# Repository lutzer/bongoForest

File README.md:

# BONGO FOREST

### Important

* Dont run arduino pros on more than 5 V on the RAW Pin. use seperate voltage regulator or **they will burn**.

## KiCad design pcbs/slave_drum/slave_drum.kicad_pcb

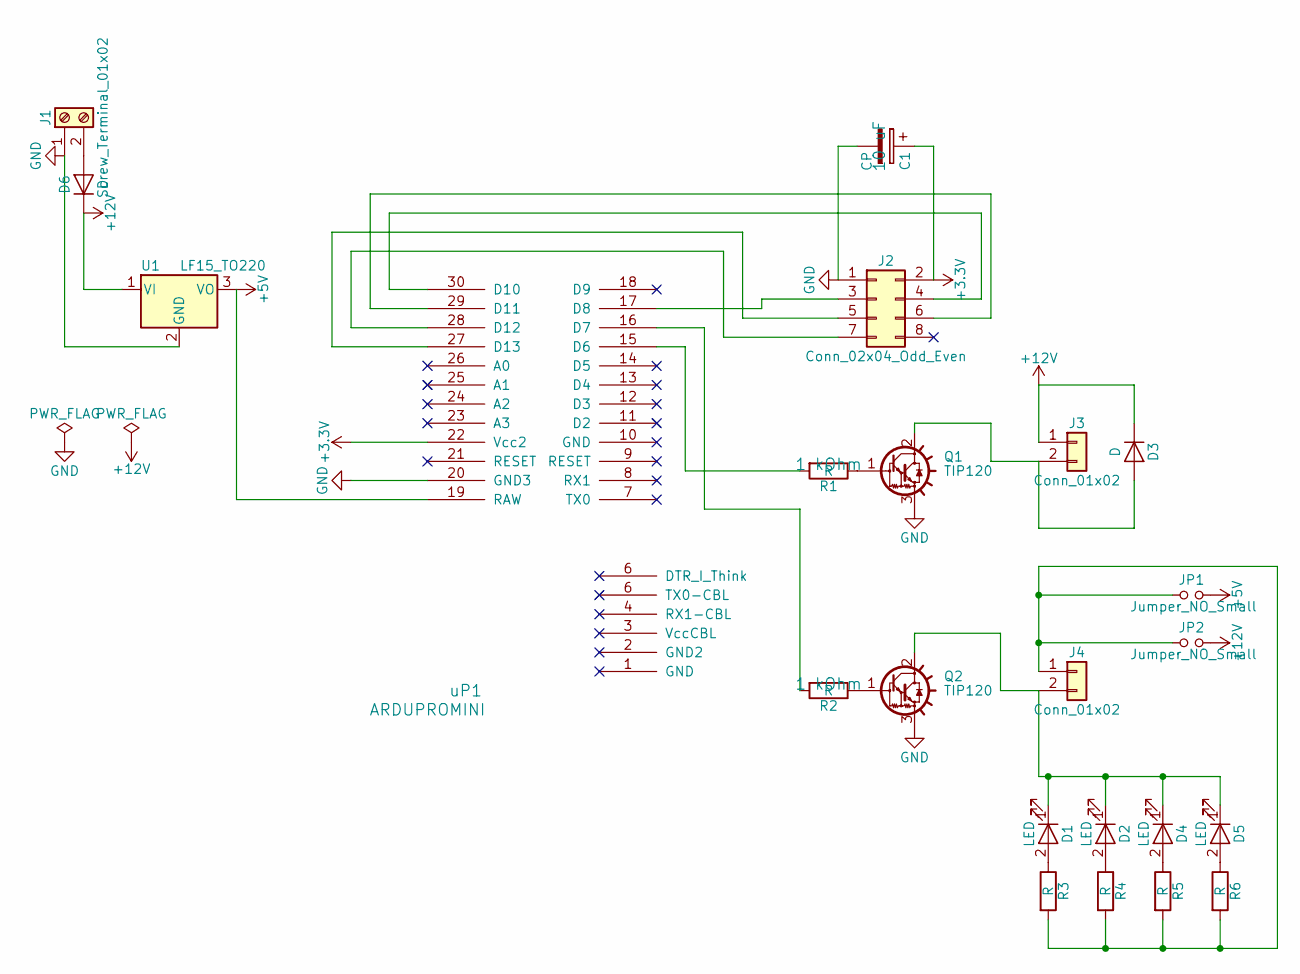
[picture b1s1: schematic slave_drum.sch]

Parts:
C1: CP; CP_Radial_D5.0mm_P2.00mm
D1, D2, D4, D5: LED; LED-5MM
D3: D; D_DO-201_P12.70mm_Horizontal
D6: D; D_DO-201AD_P12.70mm_Horizontal
J1: Screw_Terminal_01x02; TerminalBlock_4UCON_19963_02x3.5mm_Straight
J2: Conn_02x04_Odd_Even; Pin_Header_Straight_2x04
J3, J4: Conn_01x02; Pin_Header_Straight_1x02
JP1, JP2: Jumper_NO_Small; SOLDER-JUMPER_1-WAY_FAR
Q1, Q2: TIP120; TO-220_Vertical
R1, R2, R3, R4, R5, R6: R; R_Axial_DIN0207_L6.3mm_D2.5mm_P7.62mm_Horizontal
U1: LF15_TO220; TO-220_Horizontal
uP1: ARDUPROMINI; ArduProMini-6

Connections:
+3V3: C1.1, J2.2, uP1.22 (Vcc2)
+5V: JP1.2, U1.3 (VO), uP1.19 (RAW)
+12V: D3.1 (K), D6.1 (K), J3.1, JP2.2, U1.1 (VI)
GND: C1.2, J1.1, J2.1, Q1.3 (E), Q2.3 (E), U1.2 (GND), uP1.20 (GND3)
unnamed: D1.1 (K), D2.1 (K), D4.1 (K), D5.1 (K), J4.2, Q2.2 (C)
unnamed: D1.2 (A), R3.1
unnamed: D2.2 (A), R4.1
unnamed: D3.2 (A), J3.2, Q1.2 (C)
unnamed: D4.2 (A), R5.1
unnamed: D5.2 (A), R6.1
unnamed: D6.2 (A), J1.2
unnamed: J2.3, uP1.17 (D8)
unnamed: J2.4, uP1.30 (D10)
unnamed: J2.5, uP1.27 (D13)
unnamed: J2.6, uP1.29 (D11)
unnamed: J2.7, uP1.28 (D12)
unnamed: J4.1, JP1.1, JP2.1, R3.2, R4.2, R5.2, R6.2
unnamed: Q1.1 (B), R1.1
unnamed: Q2.1 (B), R2.1
unnamed: R1.2, uP1.15 (D6)
unnamed: R2.2, uP1.16 (D7)

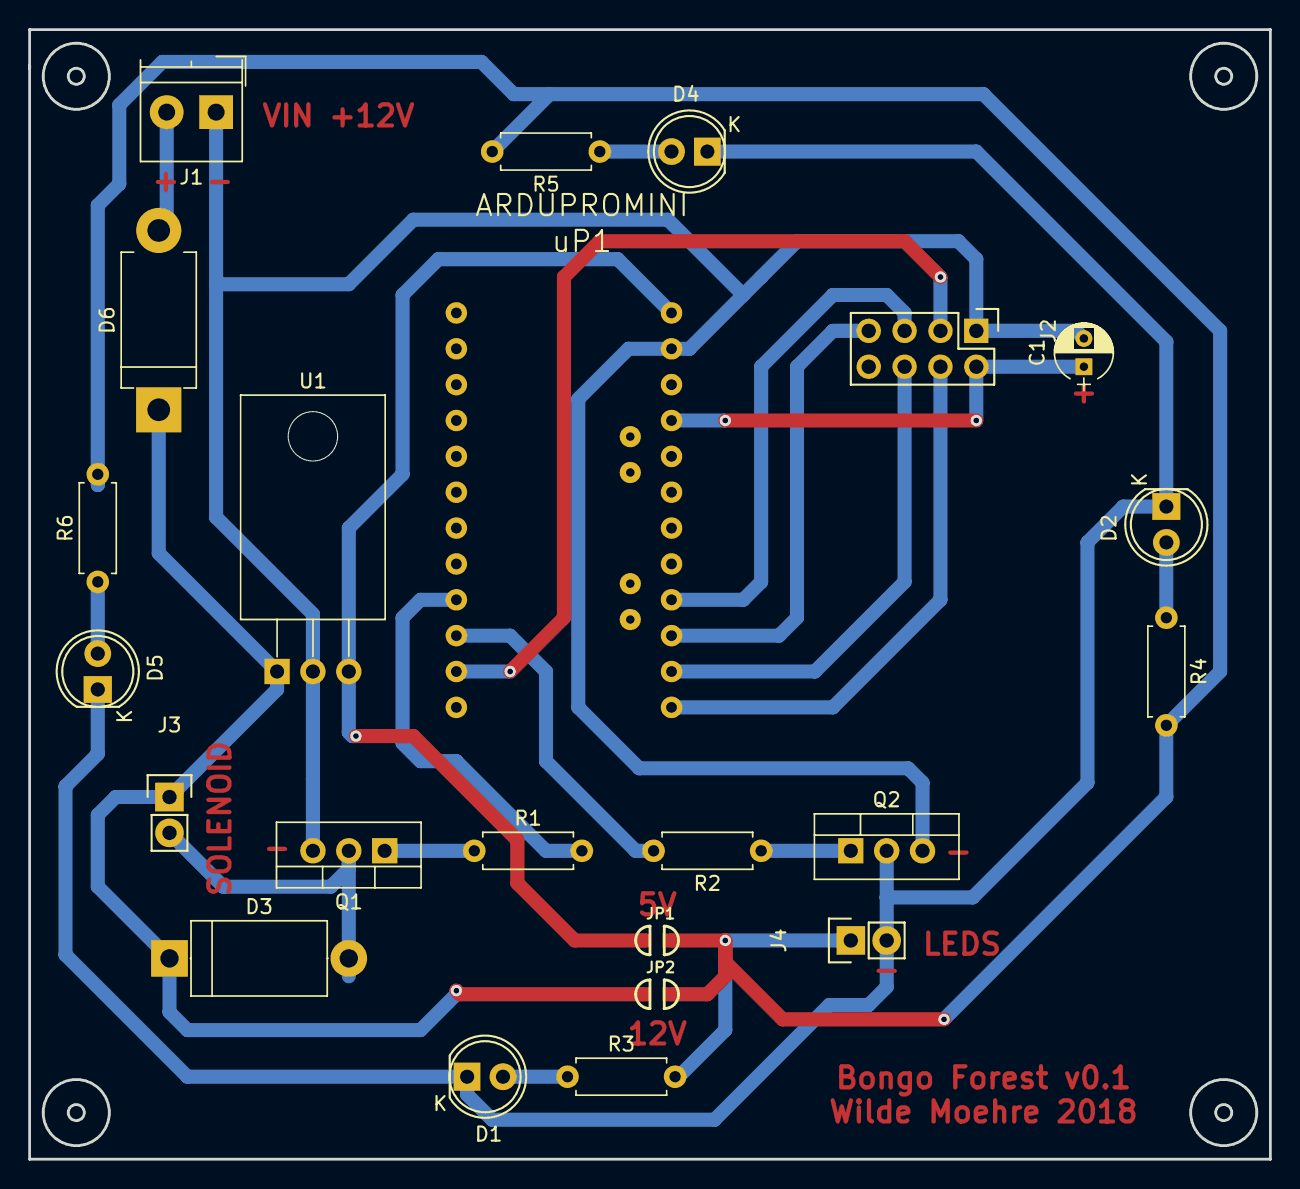
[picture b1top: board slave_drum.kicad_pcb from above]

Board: 2 copper layers, 87.9 x 80.0 mm, 23 parts (0 on the bottom side), 21 nets.

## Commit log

2018-05-25 added radio docs@
2018-06-09 created test patches
2018-06-16 added slave drum schematic
2018-06-17 finished slave pcb
2018-06-18 added bom
2018-06-22 changed arduino sketches
2018-06-25 changed 3d models
2018-06-27 updated holder and bom
2018-07-01 add master drum schematic
2018-07-10 bongoForest | master - added TIP120 and MC7800CT datasheet docs
2018-07-17 bongoForest | master - code for master drum
2018-07-17 bongoForest | master - signal filtering logic, visualization and configuration
2018-07-17 bongoForest | master - radio enabled
2018-07-21 added stls
2018-07-21 changed stls for pcb case
2018-07-22 bongoForest | master - created Main drum platform for printing
2018-07-22 changed top case
2018-07-22 set up slave platform io project
2018-07-22 bongoForest | master - radio message standar
2018-07-22 added initial version of slave sketch
2018-07-23 added changing delay time to slave code
2018-07-25 bongoForest | master - Config RF sender
2018-07-25 bongoForest | master - Control Pannel UI and bongo config logic
2018-07-25 bongoForest | master - update filtering mapping
2018-07-25 bongoForest | master - clean up
2018-07-26 bongoForest | master - implementing save/load logic
2018-08-07 added updateeeprom method to save eeprom write cycles
2018-08-07 changed readme of slave drum
2019-06-11 bongoForest | master - fest changes
2019-07-19 bongoForest | master - update pio config
2019-07-19 bongoForest | master - added a direct RF control project
2019-07-19 bongoForest | master - Direct ID control address
2019-07-19 bongoForest | master - basic procedding laser controller
